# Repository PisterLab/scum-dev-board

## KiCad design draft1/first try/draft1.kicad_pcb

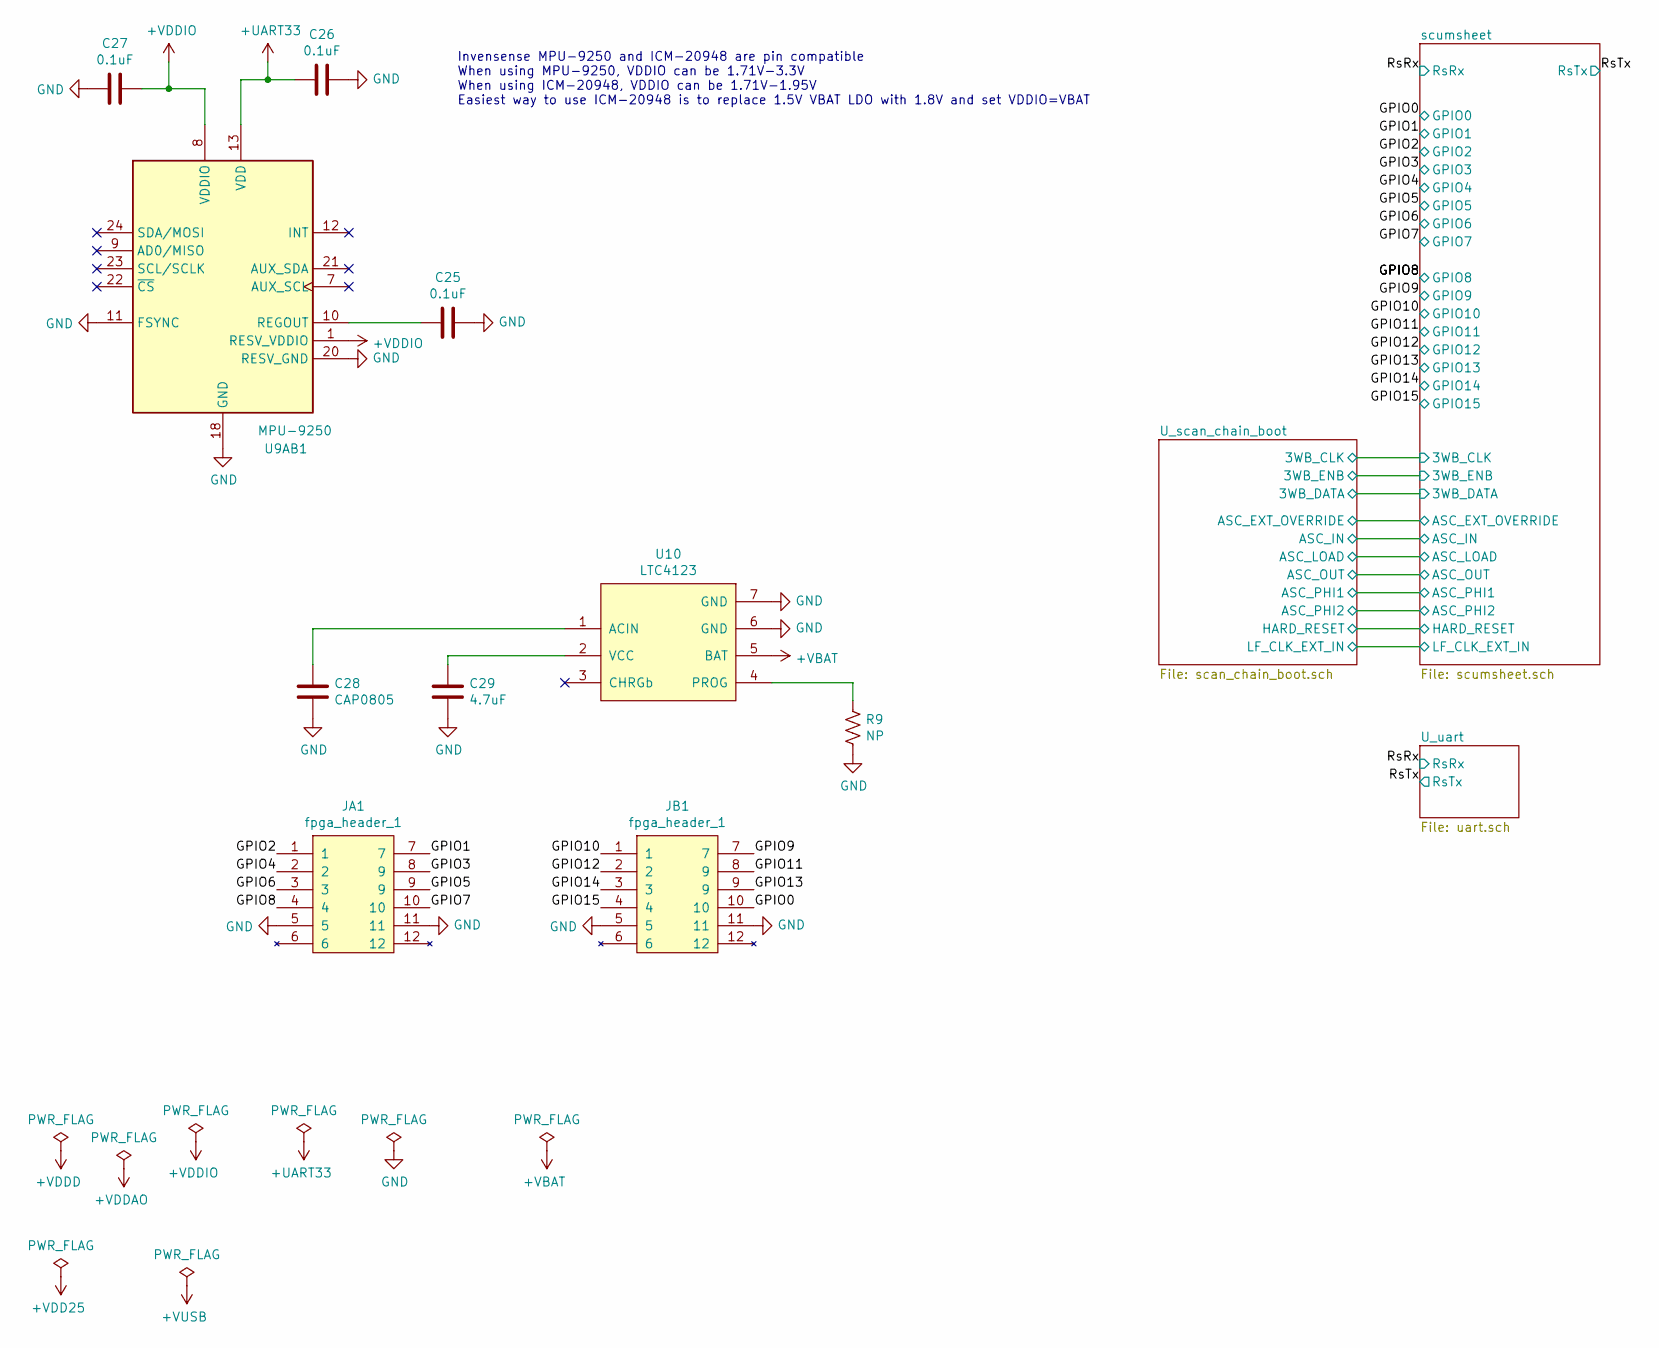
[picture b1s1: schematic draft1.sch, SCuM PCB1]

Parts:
C25, C26, C27: 0.1uF; C_0402_1005Metric
C28: CAP0805; C_0402_1005Metric
C29: 4.7uF; C_0402_1005Metric
JA1: fpga_header_1; PinHeader_2x06_P2.54mm_Vertical
JB1: fpga_header_1; PinHeader_2x06_P2.54mm_Vertical
R9: NP
U9AB1: MPU-9250; InvenSense_QFN-24_3x3mm_P0.4mm
U10: LTC4123

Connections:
+UART33: C26.1, U9AB1.13 (VDD); also elsewhere on the board
+VBAT: U10.5 (BAT); also elsewhere on the board
+VDDIO: C27.1, U9AB1.1 (RESV_VDDIO), U9AB1.8 (VDDIO); also elsewhere on the board
/GPIO0: JB1.10; also elsewhere on the board
/GPIO1: JA1.7; also elsewhere on the board
/GPIO2: JA1.1; also elsewhere on the board
/GPIO3: JA1.8 (9); also elsewhere on the board
/GPIO4: JA1.2; also elsewhere on the board
/GPIO5: JA1.9; also elsewhere on the board
/GPIO6: JA1.3; also elsewhere on the board
/GPIO7: JA1.10; also elsewhere on the board
/GPIO8: JA1.4; also elsewhere on the board
/GPIO9: JB1.7; also elsewhere on the board
/GPIO10: JB1.1; also elsewhere on the board
/GPIO11: JB1.8 (9); also elsewhere on the board
/GPIO12: JB1.2; also elsewhere on the board
/GPIO13: JB1.9; also elsewhere on the board
/GPIO14: JB1.3; also elsewhere on the board
/GPIO15: JB1.4; also elsewhere on the board
GND: C25.2, C26.2, C27.2, C28.2, C29.2, JA1.5, JA1.11, JB1.5, JB1.11, R9.2, U9AB1.11 (FSYNC), U9AB1.18 (GND), U9AB1.20 (RESV_GND), U10.6 (GND), U10.7 (GND); also elsewhere on the board
unnamed: C25.1, U9AB1.10 (REGOUT)
unnamed: C28.1, U10.1 (ACIN)
unnamed: C29.1, U10.2 (VCC)
unnamed: R9.1, U10.4 (PROG)

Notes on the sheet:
Invensense MPU-9250 and ICM-20948 are pin compatible When using MPU-9250, VDDIO can be 1.71V-3.3V When using ICM-20948, VDDIO can be 1.71V-1.95V Easiest way to use ICM-20948 is to replace 1.5V VBAT LDO with 1.8V and set VDDIO=VBAT

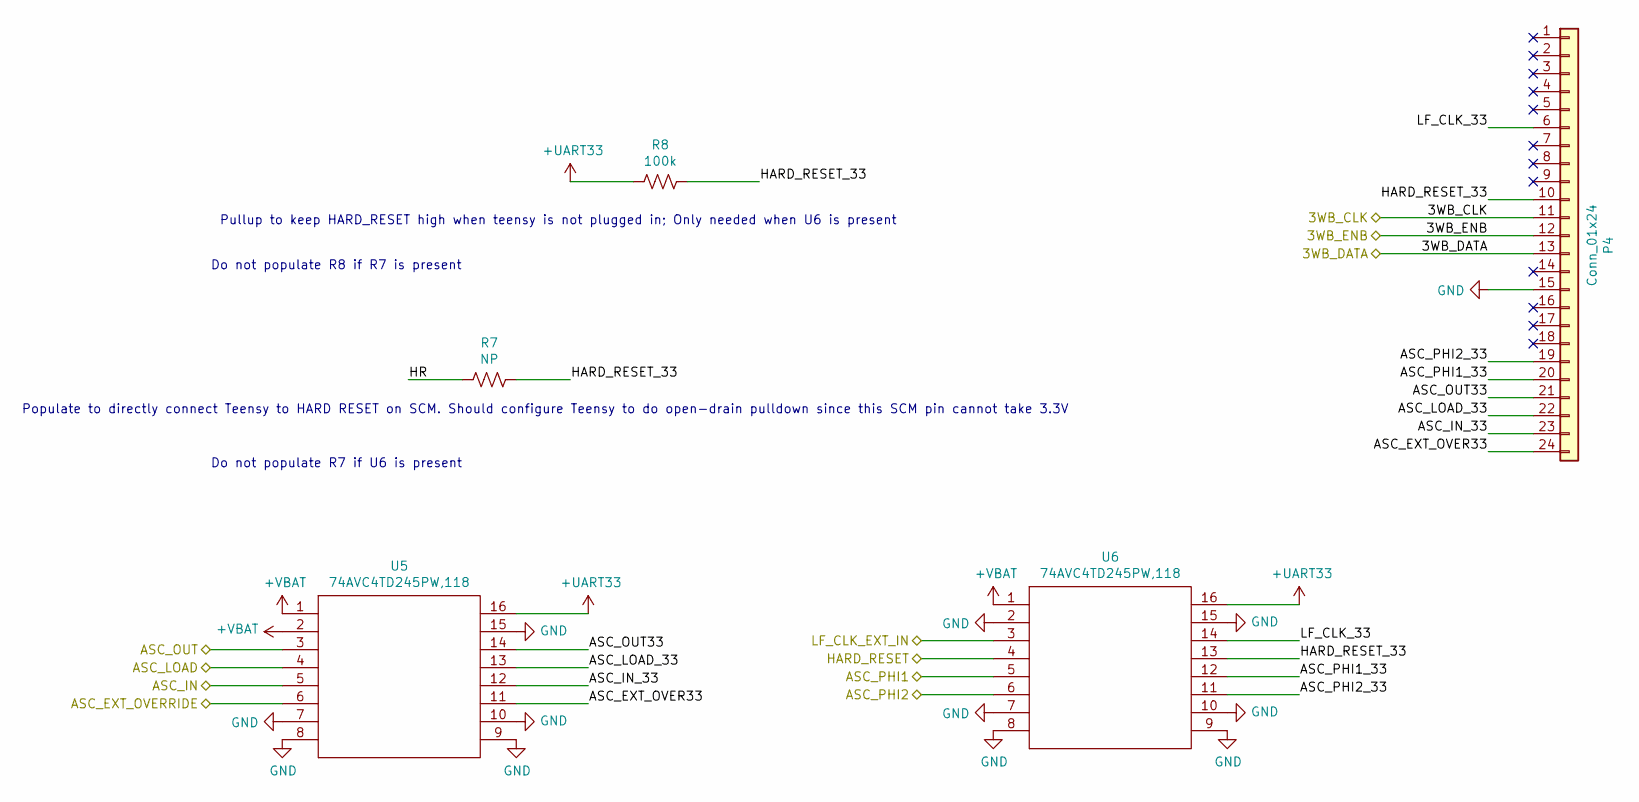
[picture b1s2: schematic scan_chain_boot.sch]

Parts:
P4: Conn_01x24; PinHeader_1x24_P2.54mm_Vertical
R7: NP; R_0603_1608Metric
R8: 100k; R_0603_1608Metric
U5, U6: 74AVC4TD245PW,118; SOP65P640X110-16N; Manufacturer_Part_Number 74AVC4TD245PW,118; Mouser Part Number 771-74AVC4TD245PW118

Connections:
+UART33: R8.2, U5.16, U6.16; also elsewhere on the board
+VBAT: U5.1, U5.2, U6.1; also elsewhere on the board
/U_scan_chain_boot/3WB_CLK: P4.11; also elsewhere on the board
/U_scan_chain_boot/3WB_DATA: P4.13; also elsewhere on the board
/U_scan_chain_boot/3WB_ENB: P4.12; also elsewhere on the board
/U_scan_chain_boot/ASC_EXT_OVER33: P4.24, U5.11
/U_scan_chain_boot/ASC_EXT_OVERRIDE: U5.6; also elsewhere on the board
/U_scan_chain_boot/ASC_IN: U5.5; also elsewhere on the board
/U_scan_chain_boot/ASC_IN_33: P4.23, U5.12
/U_scan_chain_boot/ASC_LOAD: U5.4; also elsewhere on the board
/U_scan_chain_boot/ASC_LOAD_33: P4.22, U5.13
/U_scan_chain_boot/ASC_OUT: U5.3; also elsewhere on the board
/U_scan_chain_boot/ASC_OUT33: P4.21, U5.14
/U_scan_chain_boot/ASC_PHI1: U6.5; also elsewhere on the board
/U_scan_chain_boot/ASC_PHI1_33: P4.20, U6.12
/U_scan_chain_boot/ASC_PHI2: U6.6; also elsewhere on the board
/U_scan_chain_boot/ASC_PHI2_33: P4.19, U6.11
/U_scan_chain_boot/HARD_RESET: R7.2, U6.4; also elsewhere on the board
/U_scan_chain_boot/HARD_RESET_33: P4.10, R7.1, R8.1, U6.13
/U_scan_chain_boot/LF_CLK_33: P4.6, U6.14
/U_scan_chain_boot/LF_CLK_EXT_IN: U6.3; also elsewhere on the board
GND: P4.15, U5.7, U5.8, U5.9, U5.10, U5.15, U6.2, U6.7, U6.8, U6.9, U6.10, U6.15; also elsewhere on the board

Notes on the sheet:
Pullup to keep HARD_RESET high when teensy is not plugged in; Only needed when U6 is present
Do not populate R8 if R7 is present
Populate to directly connect Teensy to HARD RESET on SCM. Should configure Teensy to do open-drain pulldown since this SCM pin cannot take 3.3V
Do not populate R7 if U6 is present

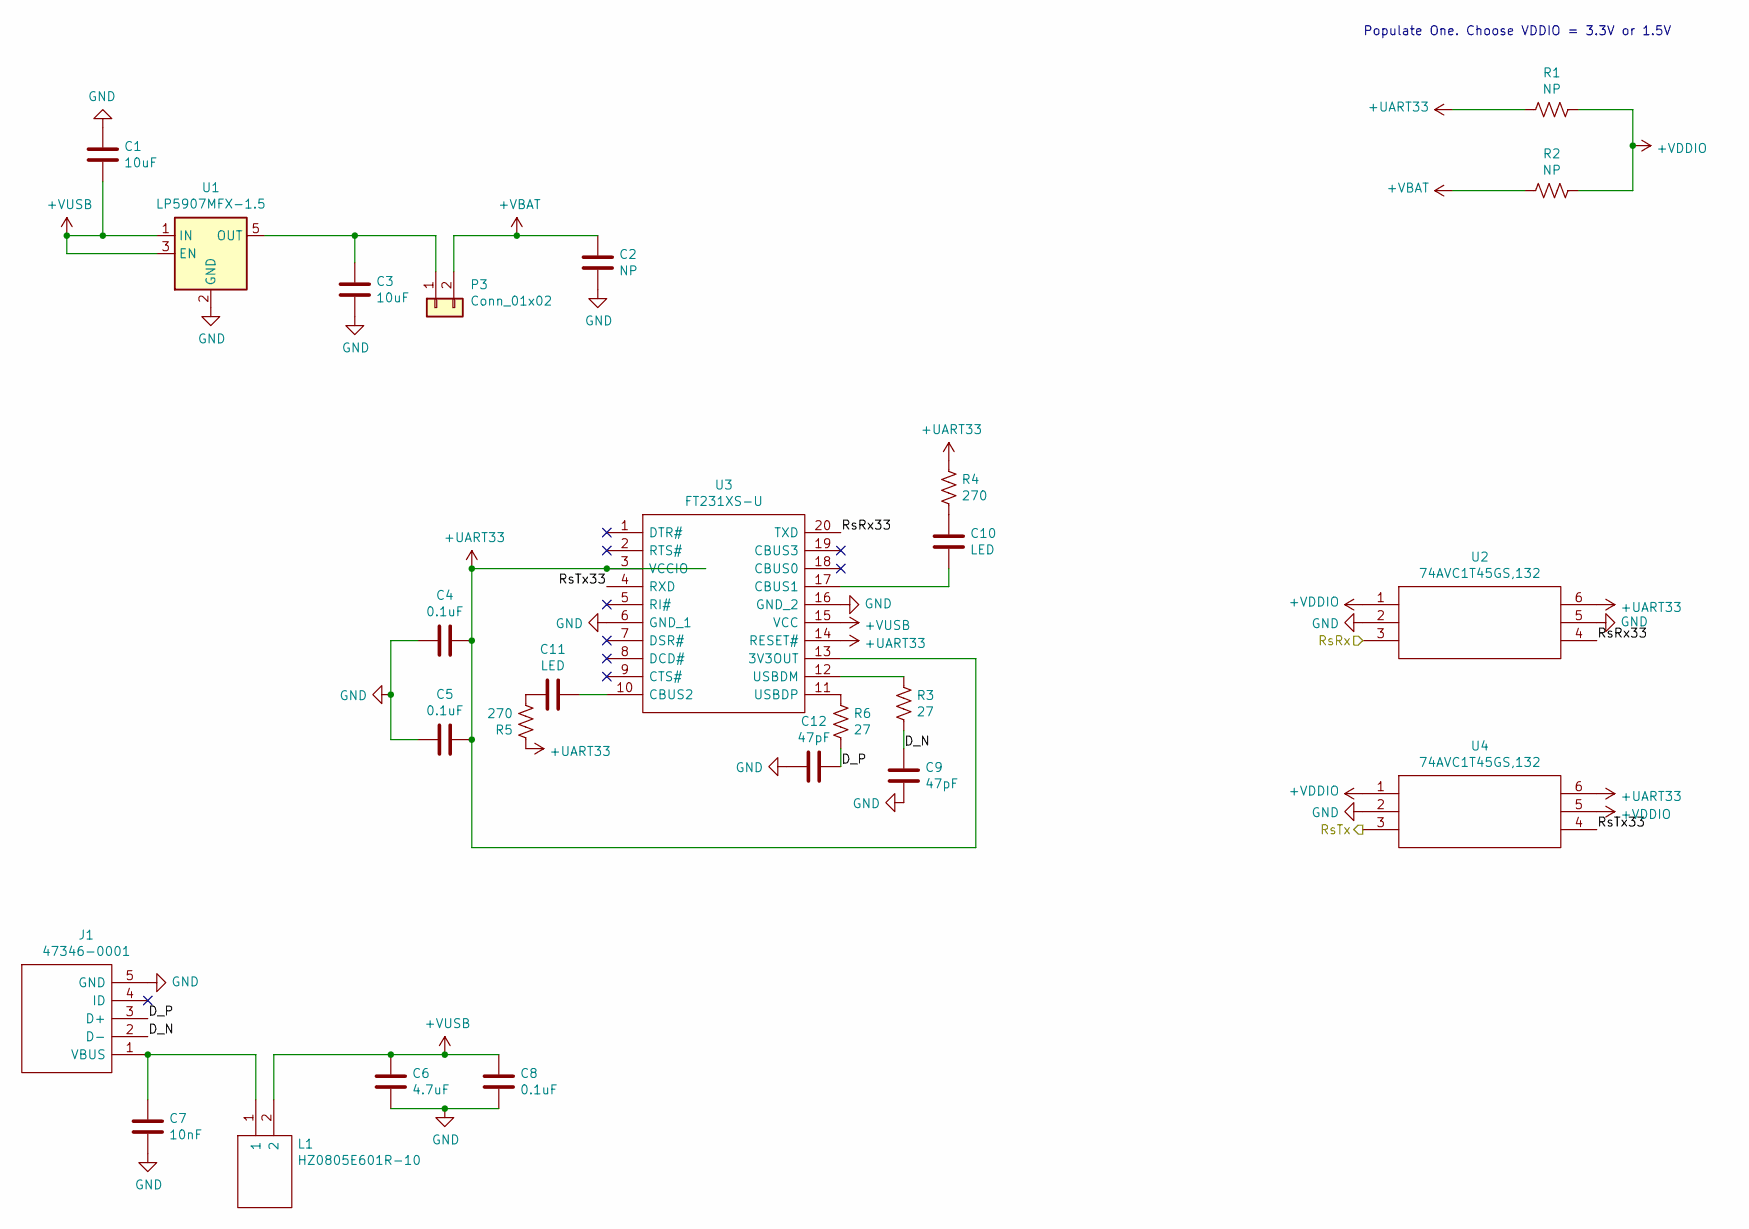
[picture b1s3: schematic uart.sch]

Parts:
C1, C3: 10uF; C_0402_1005Metric
C2: NP; C_0402_1005Metric
C4, C5, C8: 0.1uF; C_0402_1005Metric
C6: 4.7uF; C_0402_1005Metric
C7: 10nF; C_0402_1005Metric
C9, C12: 47pF; C_0402_1005Metric
C10, C11: LED; C_0402_1005Metric
J1: 47346-0001; Manufacturer_Part_Number 47346-0001; Mouser Part Number 538-47346-0001
L1: HZ0805E601R-10; Manufacturer_Part_Number HZ0805E601R-10
P3: Conn_01x02
R1, R2: NP
R3, R6: 27
R4, R5: 270
U1: LP5907MFX-1.5; SOT-23-5
U2, U4: 74AVC1T45GS,132; Manufacturer_Part_Number 74AVC1T45GS,132; Mouser Part Number 771-74AVC1T45GS132
U3: FT231XS-U; Manufacturer_Part_Number FT231XS-U; Mouser Part Number 895-FT231XS-U

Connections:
+UART33: C4.1, C5.1, R1.1, R4.1, R5.1, U2.6, U3.3 (VCCIO), U3.13 (3V3OUT), U3.14 (RESET#), U4.6; also elsewhere on the board
+VBAT: C2.1, P3.2, R2.1; also elsewhere on the board
+VDDIO: R1.2, R2.2, U2.1, U4.1, U4.5; also elsewhere on the board
+VUSB: C1.2, C6.1, C8.1, L1.2, U1.1 (IN), U1.3 (EN), U3.15 (VCC)
/RsRx: U2.3; also elsewhere on the board
/RsTx: U4.3; also elsewhere on the board
/U_uart/D_N: C9.2, J1.2 (D-), R3.2
/U_uart/D_P: C12.1, J1.3 (D+), R6.1
/U_uart/RsRx33: U2.4, U3.20 (TXD)
/U_uart/RsTx33: U3.4 (RXD), U4.4
GND: C1.1, C2.2, C3.2, C4.2, C5.2, C6.2, C7.2, C8.2, C9.1, C12.2, J1.5 (GND), U1.2 (GND), U2.2, U2.5, U3.6 (GND_1), U3.16 (GND_2), U4.2; also elsewhere on the board
unnamed: C3.1, P3.1, U1.5 (OUT)
unnamed: C7.1, J1.1 (VBUS), L1.1
unnamed: C10.1, U3.17 (CBUS1)
unnamed: C10.2, R4.2
unnamed: C11.1, R5.2
unnamed: C11.2, U3.10 (CBUS2)
unnamed: R3.1, U3.12 (USBDM)
unnamed: R6.2, U3.11 (USBDP)

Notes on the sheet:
Populate One. Choose VDDIO = 3.3V or 1.5V

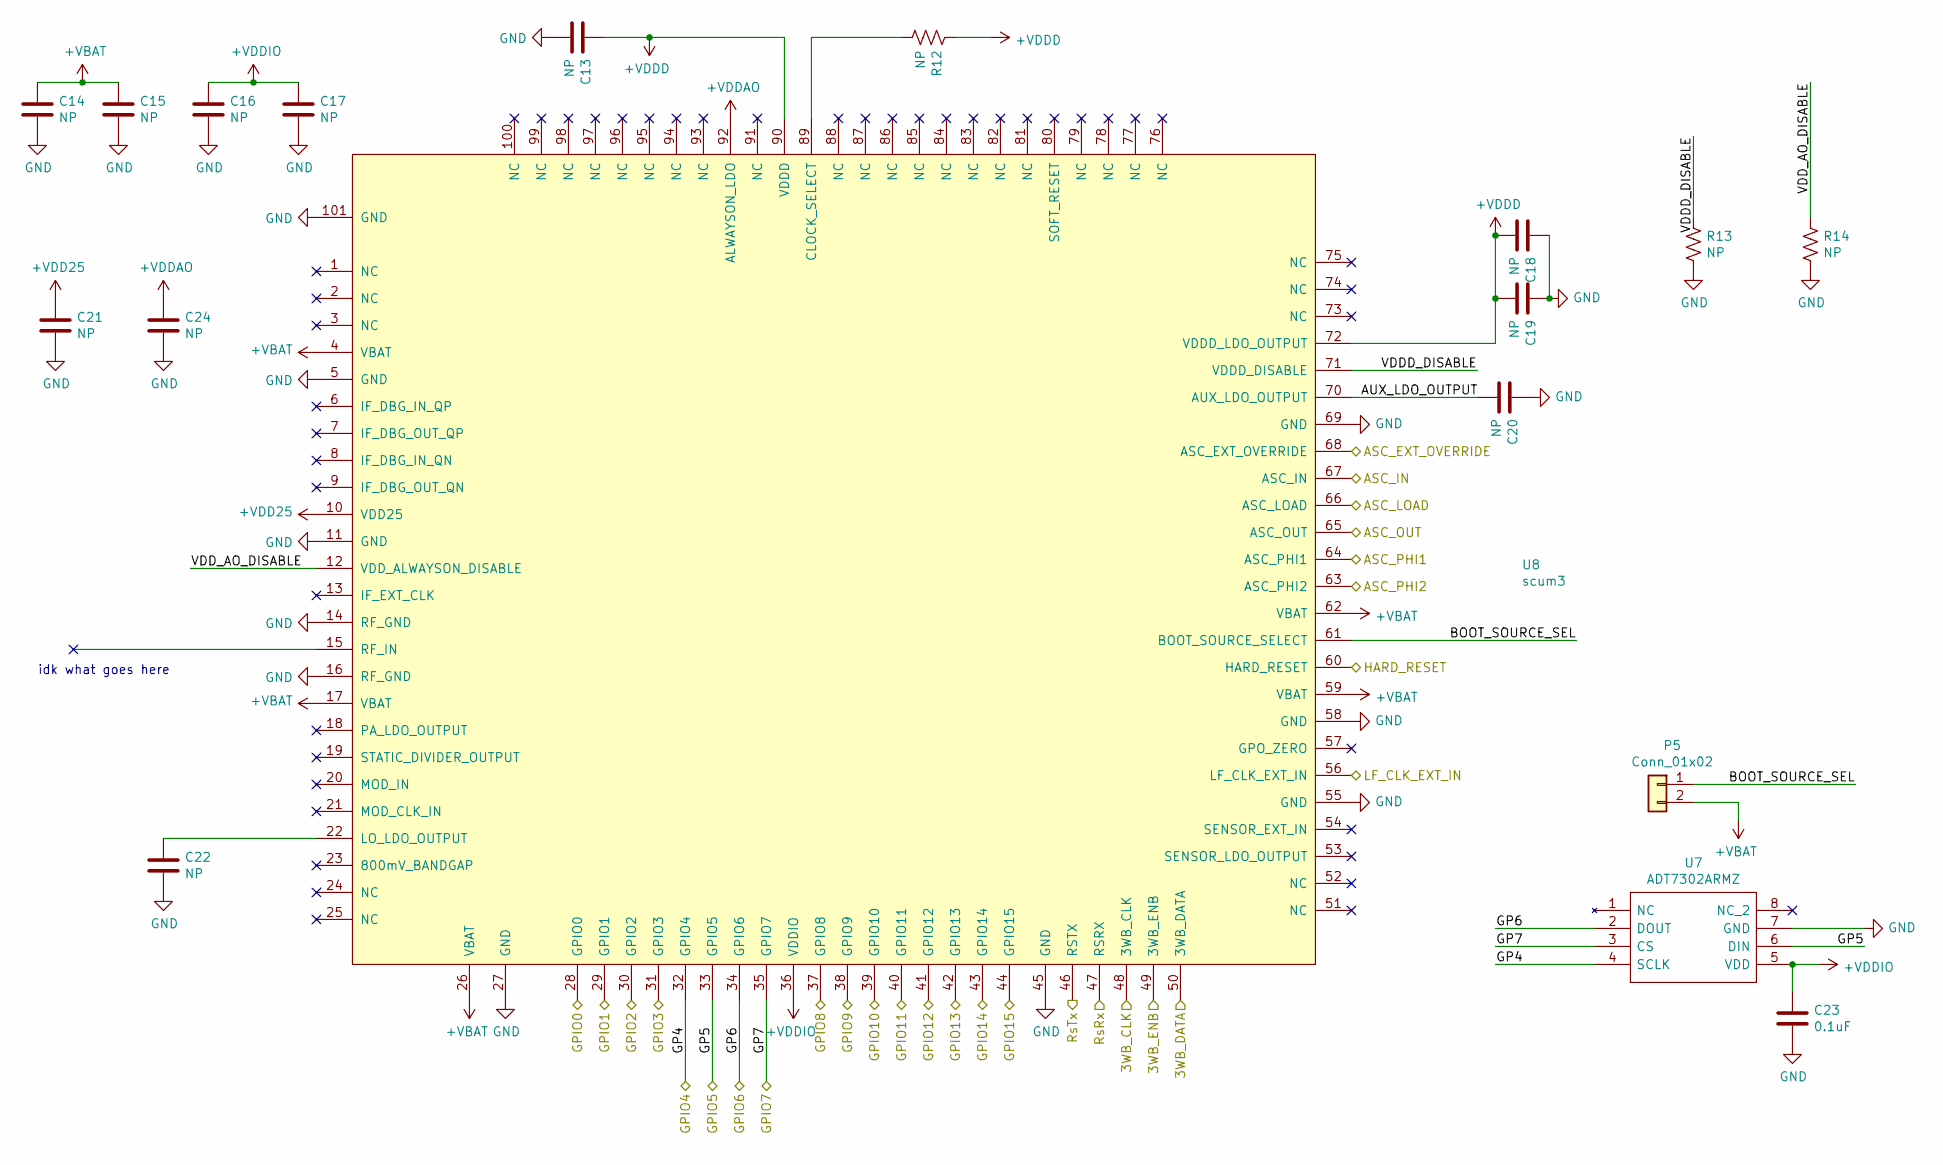
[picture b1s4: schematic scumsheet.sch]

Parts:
C13, C14, C15, C16, C17, C18, C19, C20, C21, C22, C24: NP; C_0402_1005Metric
C23: 0.1uF; C_0402_1005Metric
P5: Conn_01x02; PinHeader_1x02_P2.54mm_Vertical
R12, R13, R14: NP; R_0603_1608Metric
U7: ADT7302ARMZ; SOP65P490X110-8N; Manufacturer_Part_Number ADT7302ARMZ; Mouser Part Number 584-ADT7302ARMZ
U8: scum3

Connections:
+VBAT: C14.1, C15.1, P5.2, U8.4 (VBAT), U8.17 (VBAT), U8.26 (VBAT), U8.59 (VBAT), U8.62 (VBAT); also elsewhere on the board
+VDD25: C21.1, U8.10 (VDD25)
+VDDAO: C24.1, U8.92 (ALWAYSON_LDO)
+VDDD: C13.1, C18.2, C19.2, R12.1, U8.72 (VDDD_LDO_OUTPUT), U8.90 (VDDD)
+VDDIO: C16.1, C17.1, C23.1, U7.5 (VDD), U8.36 (VDDIO); also elsewhere on the board
/GPIO0: U8.28 (GPIO0); also elsewhere on the board
/GPIO1: U8.29 (GPIO1); also elsewhere on the board
/GPIO2: U8.30 (GPIO2); also elsewhere on the board
/GPIO3: U8.31 (GPIO3); also elsewhere on the board
/GPIO4: U7.4 (SCLK), U8.32 (GPIO4); also elsewhere on the board
/GPIO5: U7.6 (DIN), U8.33 (GPIO5); also elsewhere on the board
/GPIO6: U7.2 (DOUT), U8.34 (GPIO6); also elsewhere on the board
/GPIO7: U7.3 (CS~), U8.35 (GPIO7); also elsewhere on the board
/GPIO8: U8.37 (GPIO8); also elsewhere on the board
/GPIO9: U8.38 (GPIO9); also elsewhere on the board
/GPIO10: U8.39 (GPIO10); also elsewhere on the board
/GPIO11: U8.40 (GPIO11); also elsewhere on the board
/GPIO12: U8.41 (GPIO12); also elsewhere on the board
/GPIO13: U8.42 (GPIO13); also elsewhere on the board
/GPIO14: U8.43 (GPIO14); also elsewhere on the board
/GPIO15: U8.44 (GPIO15); also elsewhere on the board
/RsRx: U8.47 (RSRX); also elsewhere on the board
/RsTx: U8.46 (RSTX); also elsewhere on the board
/U_scan_chain_boot/3WB_CLK: U8.48 (3WB_CLK); also elsewhere on the board
/U_scan_chain_boot/3WB_DATA: U8.50 (3WB_DATA); also elsewhere on the board
/U_scan_chain_boot/3WB_ENB: U8.49 (3WB_ENB); also elsewhere on the board
/U_scan_chain_boot/ASC_EXT_OVERRIDE: U8.68 (ASC_EXT_OVERRIDE); also elsewhere on the board
/U_scan_chain_boot/ASC_IN: U8.67 (ASC_IN); also elsewhere on the board
/U_scan_chain_boot/ASC_LOAD: U8.66 (ASC_LOAD); also elsewhere on the board
/U_scan_chain_boot/ASC_OUT: U8.65 (ASC_OUT); also elsewhere on the board
/U_scan_chain_boot/ASC_PHI1: U8.64 (ASC_PHI1); also elsewhere on the board
/U_scan_chain_boot/ASC_PHI2: U8.63 (ASC_PHI2); also elsewhere on the board
/U_scan_chain_boot/HARD_RESET: U8.60 (HARD_RESET); also elsewhere on the board
/U_scan_chain_boot/LF_CLK_EXT_IN: U8.56 (LF_CLK_EXT_IN); also elsewhere on the board
/scumsheet/AUX_LDO_OUTPUT: C20.2, U8.70 (AUX_LDO_OUTPUT)
/scumsheet/BOOT_SOURCE_SEL: P5.1, U8.61 (BOOT_SOURCE_SELECT)
/scumsheet/VDDD_DISABLE: R13.1, U8.71 (VDDD_DISABLE)
/scumsheet/VDD_AO_DISABLE: R14.1, U8.12 (VDD_ALWAYSON_DISABLE)
GND: C13.2, C14.2, C15.2, C16.2, C17.2, C18.1, C19.1, C20.1, C21.2, C22.2, C23.2, C24.2, R13.2, R14.2, U7.7 (GND), U8.5 (GND), U8.11 (GND), U8.14 (RF_GND), U8.16 (RF_GND), U8.27 (GND), U8.45 (GND), U8.55 (GND), U8.58 (GND), U8.69 (GND), U8.101 (GND); also elsewhere on the board
unnamed: C22.1, U8.22 (LO_LDO_OUTPUT)
unnamed: R12.2, U8.89 (CLOCK_SELECT)

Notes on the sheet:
idk what goes here

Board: 2 copper layers, 58 parts (16 on the bottom side), 67 nets, no tracks yet.

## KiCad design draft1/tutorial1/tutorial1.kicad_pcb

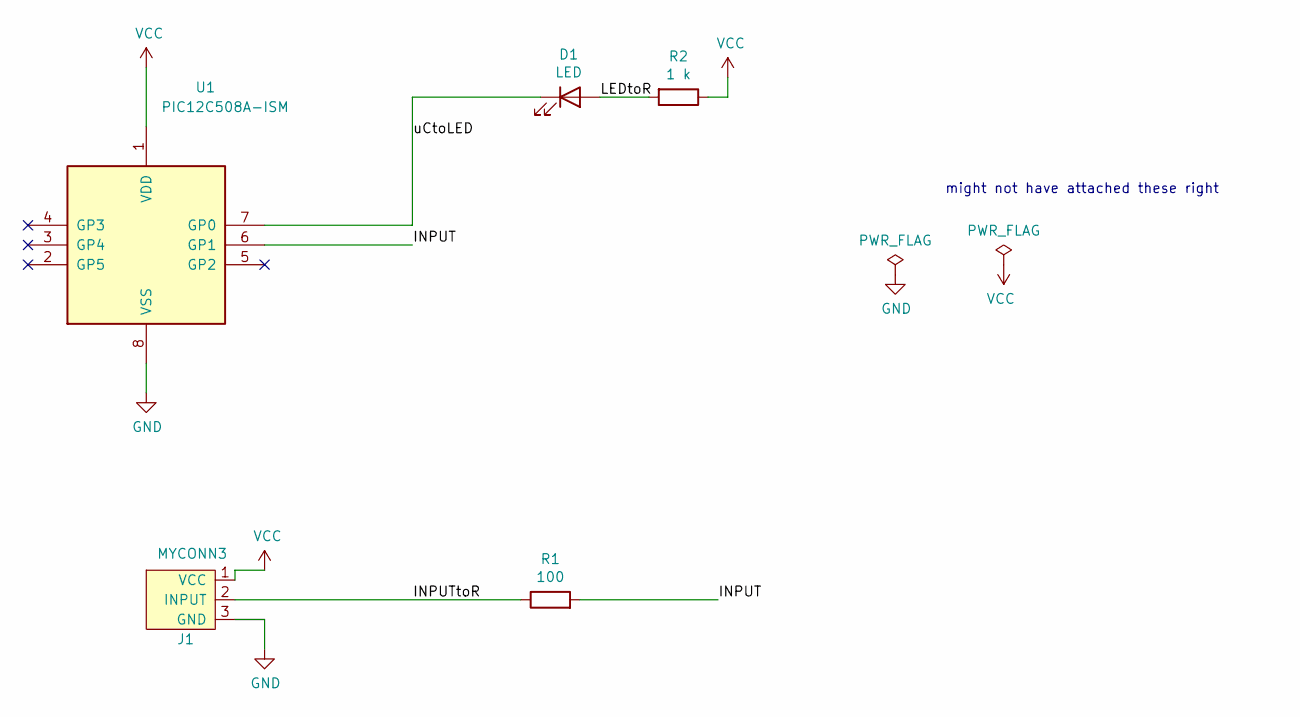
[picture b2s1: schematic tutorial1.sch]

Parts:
D1: LED
J1: MYCONN3
R1: 100
R2: 1 k
U1: PIC12C508A-ISM; DIP-8_W7.62mm

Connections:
/INPUT: R1.2, U1.6 (GP1)
/INPUTtoR: J1.2 (INPUT), R1.1
/LEDtoR: D1.2 (A), R2.2
/uCtoLED: D1.1 (K), U1.7 (GP0)
GND: J1.3 (GND), U1.8 (VSS)
VCC: J1.1 (VCC), R2.1, U1.1 (VDD)

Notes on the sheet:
might not have attached these right

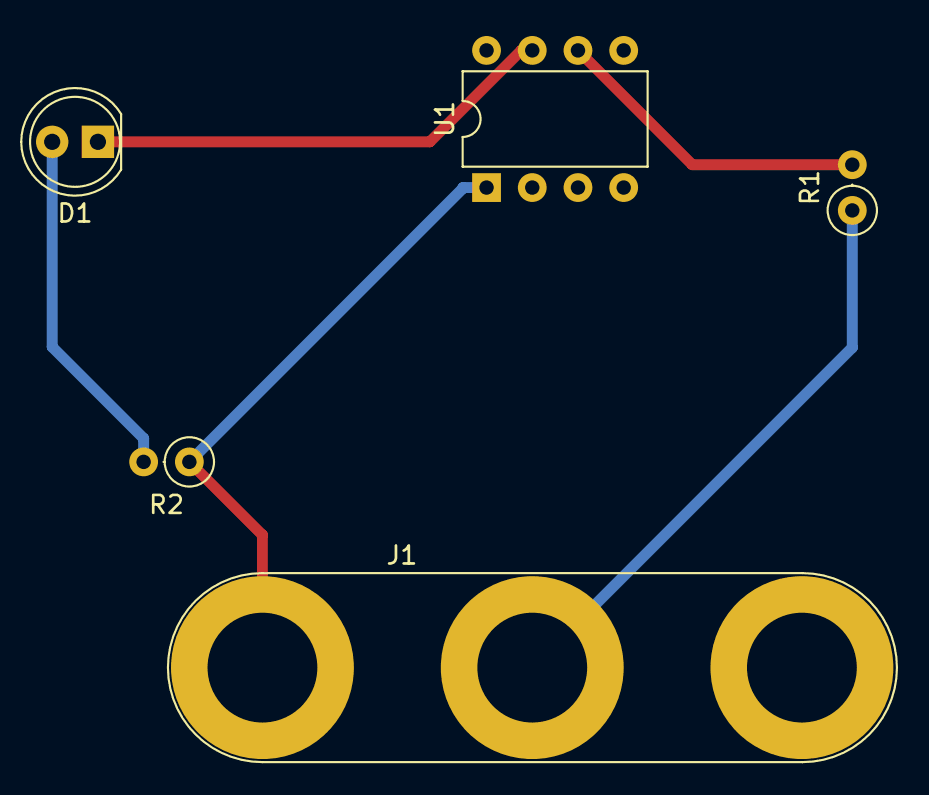
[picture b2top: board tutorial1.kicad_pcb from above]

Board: 2 copper layers, 5 parts (0 on the bottom side), 6 nets.

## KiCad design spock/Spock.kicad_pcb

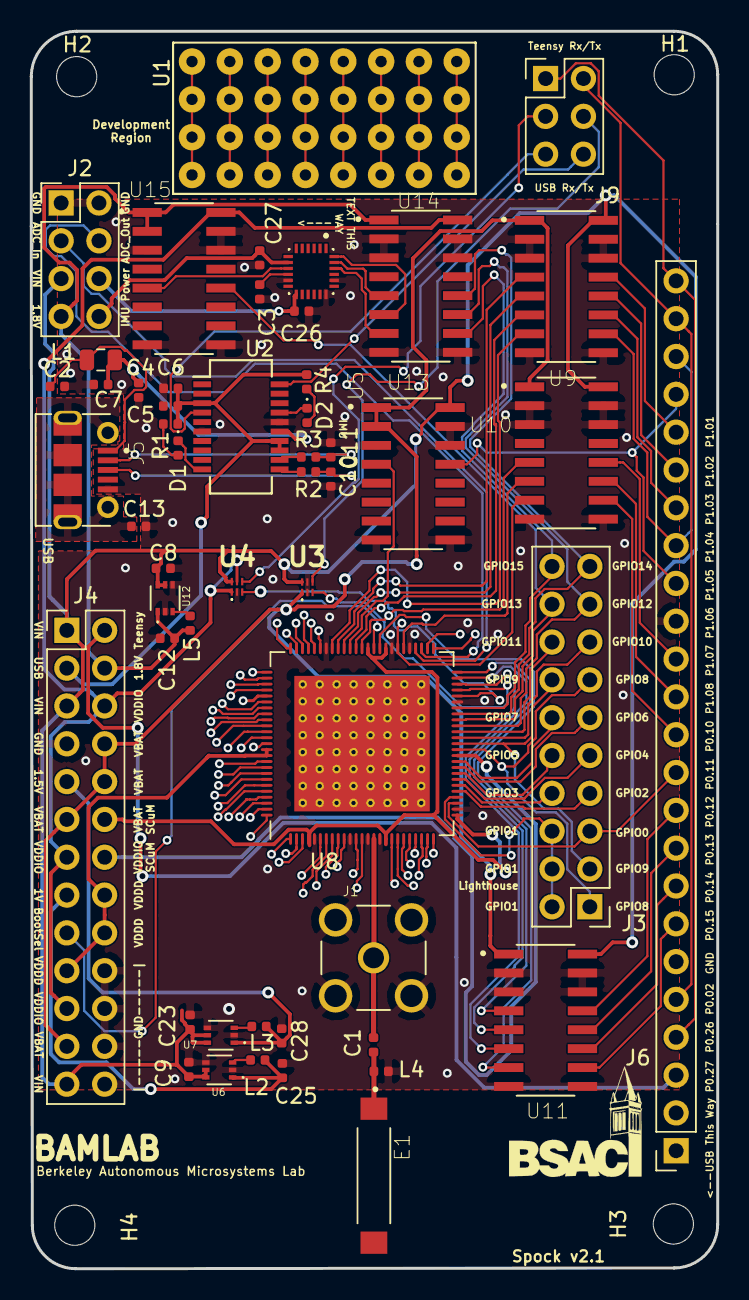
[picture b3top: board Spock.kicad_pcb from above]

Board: 2 copper layers, 46.1 x 83.1 mm, 56 parts (0 on the bottom side), 94 nets.

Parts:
C1: 1.5 pF; C_0402_1005Metric
C2: 10nF; C_0402_1005Metric
C3, C5, C6, C7, C26, C27: 0.1uF; C_0402_1005Metric
C4: 4.7uF; C_0402_1005Metric
C8, C9, C12, C23, C25, C28: 10 uF; C_0402_1005Metric
C10, C11: 47pF; C_0402_1005Metric
C13: C; C_0402_1005Metric
D1, D2: LED; LED_0402_1005Metric
E1: 2450AT45A100E; ANT_2450AT45A100E
H1, H2, H3, H4: MountingHole; MountingHole_2.7mm_M2.5
J1: CONSMA001-G; LINX_CONSMA001-G
J2: Conn_02x04_Odd_Even; PinHeader_2x04_P2.54mm_Vertical
J3: Conn_02x10_Odd_Even; PinHeader_2x10_P2.54mm_Vertical
J4: Conn_02x13_Odd_Even; PinHeader_2x13_P2.54mm_Vertical
J5: 1050170001; MOLEX_1050170001
J6: Conn_01x24; PinSocket_1x24_P2.54mm_Vertical
J9: Conn_02x03_Odd_Even; PinHeader_2x03_P2.54mm_Vertical
L1: HZ0805E601R-10; L_0805_2012Metric
L2, L3, L5: 2.2 uH; L_0402_1005Metric
L4: 3.9 nH; L_0402_1005Metric
R1, R4: 270; R_0402_1005Metric
R2, R3: 27; R_0402_1005Metric
U1: Perfboard
U2: FT231XS-U; SSOP-20_3.9x8.7mm_P0.635mm
U3, U4: 74AVC1T45GS-Q100H; 74LVC1G3157GS132
U5: ICM-20948; QFN40P300X300X105-24N
U6: S-85S1AB10-I6T1U; SOFL50P180X50-6N
U7: S-85S1AB15-I6T1U; SOFL50P180X50-6N
U8: scum3; QFN-100_EP_12x12_Pitch0.4mm
U9, U10, U11, U13, U14, U15: 74AVCH4T245D,118; SOIC127P600X175-16N
U12: S-85S1AB18-I6T1U; SOFL50P180X50-6N

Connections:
+1VIN: C25.1, J4.15, L2.1, U6.1
+15VIN: C28.1, J4.9, L3.1, U7.1
+TEENSY33: J4.2, J6.3
+USB33: C5.1, C6.1, J4.3, R1.1, R4.1, U2.3, U2.13, U2.14
+V18IO: C12.1, J2.7, J4.4, L5.1, U12.1, U14.1, U15.1, U15.2
+V18IO_IMU: C27.1, J2.8, U5.8
+VBAT: J4.8, J4.10, J4.11, J4.23, U3.1, U9.1, U10.1, U11.1, U13.1, U13.2
+VBATSCuM: J4.12, U8.4, U8.17, U8.26, U8.59, U8.62
+VDDD: J4.16, J4.18, J4.19, U8.89, U8.90
+VDDIO: J4.6, J4.13, J4.21, U4.1, U4.5, U14.16, U15.16
+VDDIOSCuM: J4.14, U8.36
+VIN: C8.1, C9.1, C23.1, J2.5, J4.1, J4.5, J4.25, U3.6, U4.6, U6.5, U6.6, U7.5, U7.6, U9.16, U10.16, U11.16, U12.5, U12.6, U13.16
+VIN_IMU: C26.1, J2.6, U5.13
+VUSB: C4.1, C7.1, L1.2, U2.15
/3WB_CLK: U8.48, U11.6
/3WB_DATA: U8.50, U11.4
/3WB_ENB: U8.49, U11.5
/ADC_IN: J2.3, U8.54
/ADC_LDO_OUT: J2.4, U8.53
/Boot_Source_Sel: J4.17, U8.61
/Clock: U8.56, U10.6
/GPIO0: J3.5, J6.11, U8.28
/GPIO1: J3.2, J3.4, J3.6, U8.29
/GPIO2: J3.7, U8.30
/GPIO3: J3.8, U8.31
/GPIO4: J3.9, U8.32
/GPIO5: J3.10, U8.33
/GPIO6: J3.11, U8.34
/GPIO7: J3.12, U8.35
/GPIO8: J3.1, J3.13, U8.37
/GPIO9: J3.3, J3.14, U8.38
/GPIO10: J3.15, U8.39
/GPIO11: J3.16, U8.40
/GPIO12: J3.17, U8.41, U14.11
/GPIO12_IMU: U5.24, U14.6
/GPIO13: J3.18, U8.42, U15.12
/GPIO13_IMU: U5.9, U15.5
/GPIO14: J3.19, U8.43, U14.12
/GPIO14_IMU: U5.23, U14.5
/GPIO15: J3.20, U8.44, U14.10
/GPIO15_IMU: U5.22, U14.7
/GPO_ZERO: U8.57, U10.7
/RF_IN: C1.2, J1.1, U8.15
/RsRx: U3.3, U8.47
/RsTx: U4.3, U8.46
/Rx33: J6.5, J6.23, J9.2
/Teensy Connections/3WB_CLK33: J6.8, U11.11
/Teensy Connections/3WB_DATA33: J6.10, U11.13
/Teensy Connections/3WB_ENB33: J6.9, U11.12
/Teensy Connections/Clock33: J6.13, U10.11
/Teensy Connections/GPO_ZERO33: J6.12, U10.10
/Teensy Connections/aLOAD33: J6.19, U9.12
/Teensy Connections/aPHI33: J6.18, U9.11
/Teensy Connections/aPHIb33: J6.14, U10.12
/Teensy Connections/aSCANIN33: J6.20, U9.13
/Teensy Connections/aSCANOUT33: J6.16, J6.21, U13.13
/Teensy Connections/aSCSEL33: J6.17, J6.22, U9.10
/Teensy Connections/hReset33: J6.7, U11.10
/Tx33: J6.4, J6.24, J9.1
/UART/D_N: C11.2, J5.2, R3.2
/UART/D_P: C10.1, J5.3, R2.1
/UART/RsRx33: J9.4, U3.4
/UART/RsRx33USB: J9.6, U2.20
/UART/RsTx33: J9.3, U4.4
/UART/RsTx33USB: J9.5, U2.4
/aLOAD: U8.66, U9.5
/aPHI: U8.64, U9.6
/aPHIb: U8.63, U10.5
/aSCANIN: U8.67, U9.4
/aSCANOUT: U8.65, U13.4
/aSCSEL: U8.68, U9.7
/hReset: U8.60, U11.7
GND: C2.2, C3.1, C4.2, C5.2, C6.2, C7.2, C8.2, C9.2, C10.2, C11.1, C12.2, C13.2, C23.2, C25.2, C26.2, C27.2, C28.2, J1.S1, J1.S2, J1.S3, J1.S4, J2.1, J2.2, J4.7, J4.20, J4.22, J4.24, J4.26, J5.5, J6.6, J6.15, L4.2, U2.6, U2.16, U3.2, U3.5, U4.2, U5.11, U5.18, U5.20, U6.2, U6.4, U7.2, U7.4, U8.5, U8.11, U8.14, U8.16, U8.27, U8.45, U8.55, U8.58, U8.69, U8.101, U9.2, U9.3, U9.8, U9.9, U9.14, U9.15, U10.2, U10.3, U10.8, U10.9, U10.14, U10.15, U11.2, U11.3, U11.8, U11.9, U11.14, U11.15, U12.2, U12.4, U13.3, U13.8, U13.9, U13.14, U13.15, U14.2, U14.3, U14.8, U14.9, U14.14, U14.15, U15.3, U15.8, U15.9, U15.14, U15.15
unnamed: C1.1, E1.1, L4.1
unnamed: C2.1, J5.1, L1.1
unnamed: C3.2, U5.10
unnamed: C13.1, J5.SH1, J5.SH2, J5.SH3, J5.SH4, J5.SH5, J5.SH6, J5.SH7, J5.SH8
unnamed: D1.1, U2.10
unnamed: D1.2, R1.2
unnamed: D2.1, U2.17
unnamed: D2.2, R4.2
unnamed: L2.2, U6.3
unnamed: L3.2, U7.3
unnamed: L5.2, U12.3
unnamed: R2.2, U2.11
unnamed: R3.1, U2.12
unnamed: U1.11, U1.21, U1.31, U1.41
unnamed: U1.12, U1.22, U1.32, U1.42
unnamed: U1.13, U1.23, U1.33, U1.43
unnamed: U1.14, U1.24, U1.34, U1.44
unnamed: U1.15, U1.25, U1.35, U1.45
unnamed: U1.16, U1.26, U1.36, U1.46
unnamed: U1.17, U1.27, U1.37, U1.47
unnamed: U1.18, U1.28, U1.38, U1.48

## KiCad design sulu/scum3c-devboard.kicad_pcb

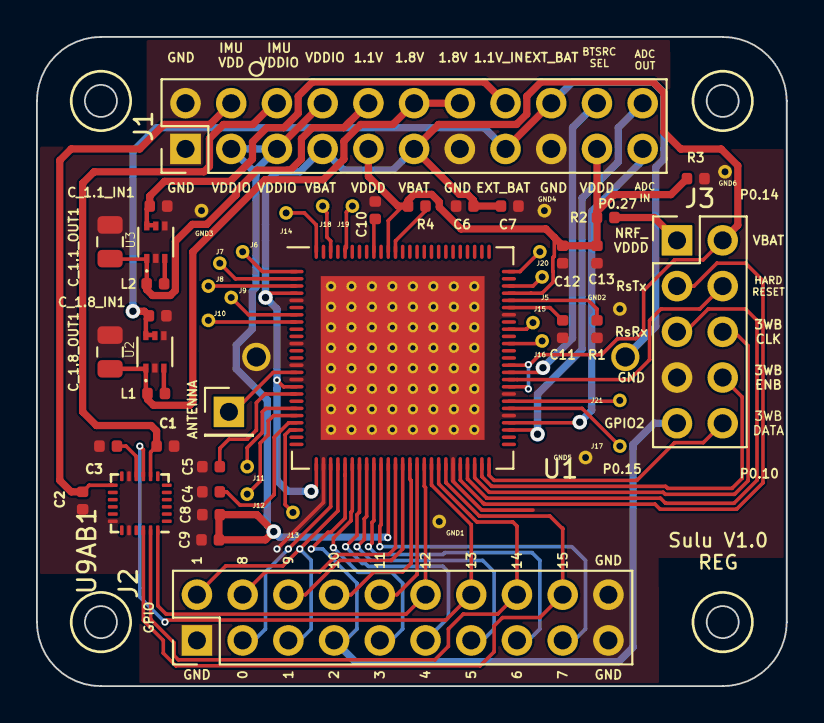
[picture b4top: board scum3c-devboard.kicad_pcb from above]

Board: 2 copper layers, 41.7 x 36.1 mm, 55 parts (1 on the bottom side), 63 nets.

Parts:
BT1: BH1000G
C1, C2, C3: 0.1uF; C_0402_1005Metric
C4, C5, C6, C7, C8, C9, C10, C11, C12, C13: NP; C_0402_1005Metric
C_1.1_IN1, C_1.8_IN1: 10 uF; C_0402_1005Metric
C_1.1_OUT1, C_1.8_OUT1: 100 uF; C_0805_2012Metric
GND1, GND2, GND3, GND4, GND5, GND6: through_hole
J1: Conn_02x11_Odd_Even; PinHeader_2x11_P2.54mm_Vertical
J2: Conn_02x10_Odd_Even; PinHeader_2x10_P2.54mm_Vertical
J3: Conn_02x05_Odd_Even; PinHeader_2x05_P2.54mm_Vertical
J4: Conn_01x01_Male; PinHeader_1x01_P2.54mm_Vertical
J5, J6, J7, J8, J9, J10, J11, J12, J13, J14, J15, J16, J17, J18, J19, J20, J21: through_hole
L1, L2: 2.2 uH; L_0402_1005Metric
R1: NP; R_0402_1005Metric
R2, R3: R_Small_US; R_0402_1005Metric
R4: 0 Ohm; R_0402_1005Metric
U1: scum3; QFN-100_EP_12x12_Pitch0.4mm_Margin0.25mm
U2: S-85S1AB18-I6T1U; SOFL50P180X50-6N
U3: S-85S1AB11-I6T1U; SOFL50P180X50-6N
U9AB1: ICM-20948; InvenSense_QFN-24_3x3mm_P0.4mm

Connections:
+1.1V_REG: C_1.1_OUT1.2, J1.10, L2.1, U3.1
+1.8V_REG: C_1.8_OUT1.2, J1.12, J1.14, L1.1, U2.1
+EXT_BAT: BT1.2, C_1.8_IN1.1, J1.15, J1.18, U2.5, U2.6
+NRF_VDDD: J3.1, R2.1
+VBAT: C6.1, C7.1, J1.7, J1.11, J3.2, U1.4, U1.17, U1.26, U1.59, U1.62
+VDDAO: C10.1, U1.92
+VDDD: C12.2, C13.2, J1.9, J1.19, R2.2, R3.1, R4.1, U1.72, U1.90
+VDDIO: C8.1, C9.1, J1.3, J1.5, J1.8, U1.36
/1.1V_IN: C_1.1_IN1.1, J1.16, U3.5, U3.6
/3WB_CLK: J3.6, U1.48
/3WB_DATA: J3.10, U1.50
/3WB_ENB: J3.8, U1.49
/ANTENNA: J4.1, U1.15
/BOOT_SOURCE_SEL: J1.20, U1.61
/GPIO0: J2.3, U1.28
/GPIO1: J2.2, J2.5, U1.29
/GPIO2: J2.7, J3.9, U1.30
/GPIO3: J2.9, U1.31
/GPIO4: J2.11, U1.32
/GPIO5: J2.13, U1.33
/GPIO6: J2.15, U1.34
/GPIO7: J2.17, U1.35
/GPIO8: J2.4, U1.37
/GPIO9: J2.6, U1.38
/GPIO10: J2.8, U1.39
/GPIO11: J2.10, U1.40
/GPIO12: J2.12, U1.41, U9AB1.24
/GPIO13: J2.14, U1.42, U9AB1.9
/GPIO14: J2.16, U1.43, U9AB1.23
/GPIO15: J2.18, U1.44, U9AB1.22
/HARD_RESET: J3.4, U1.60
/IMU_VDD: C2.1, J1.4, U9AB1.13
/IMU_VDDIO: C1.1, J1.6, U9AB1.8
/RsRx: J3.5, U1.47
/RsTx: J3.3, U1.46
/SENSOR_EXT_IN: J1.21, U1.54
/SENSOR_LDO_OUTPUT: J1.22, U1.53
/scumsheet/AUX_LDO_OUTPUT: C11.2, U1.70
/scumsheet/LO_LDO_OUTPUT: C4.1, U1.22
/scumsheet/PA_LDO_OUTPUT: C5.1, U1.18
/scumsheet/VDDD_DISABLE: R1.1, U1.71
GND: BT1.1, C1.2, C2.2, C3.2, C4.2, C5.2, C6.2, C7.2, C8.2, C9.2, C10.2, C11.1, C12.1, C13.1, C_1.1_IN1.2, C_1.1_OUT1.1, C_1.8_IN1.2, C_1.8_OUT1.1, GND1.1, GND2.1, GND3.1, GND4.1, GND5.1, GND6.1, J1.1, J1.2, J1.13, J1.17, J2.1, J2.19, J2.20, J3.7, R1.2, R3.2, U1.5, U1.11, U1.14, U1.16, U1.27, U1.45, U1.55, U1.58, U1.69, U1.101, U2.2, U2.4, U3.2, U3.4, U9AB1.11, U9AB1.18, U9AB1.20
unnamed: C3.1, U9AB1.10
unnamed: J5.1, U1.73
unnamed: J6.1, U1.1
unnamed: J7.1, U1.2
unnamed: J8.1, U1.3
unnamed: J9.1, U1.7
unnamed: J10.1, U1.8
unnamed: J11.1, U1.20
unnamed: J12.1, U1.21
unnamed: J13.1, U1.23
unnamed: J14.1, U1.100
unnamed: J15.1, U1.67
unnamed: J16.1, U1.65
unnamed: J17.1, U1.56
unnamed: J18.1, U1.98
unnamed: J19.1, U1.96
unnamed: J20.1, U1.75
unnamed: J21.1, U1.57
unnamed: L1.2, U2.3
unnamed: L2.2, U3.3
unnamed: R4.2, U1.89

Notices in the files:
parts and their libraries:
Copyright 2021 Accelerated Designs. All rights reserved.
